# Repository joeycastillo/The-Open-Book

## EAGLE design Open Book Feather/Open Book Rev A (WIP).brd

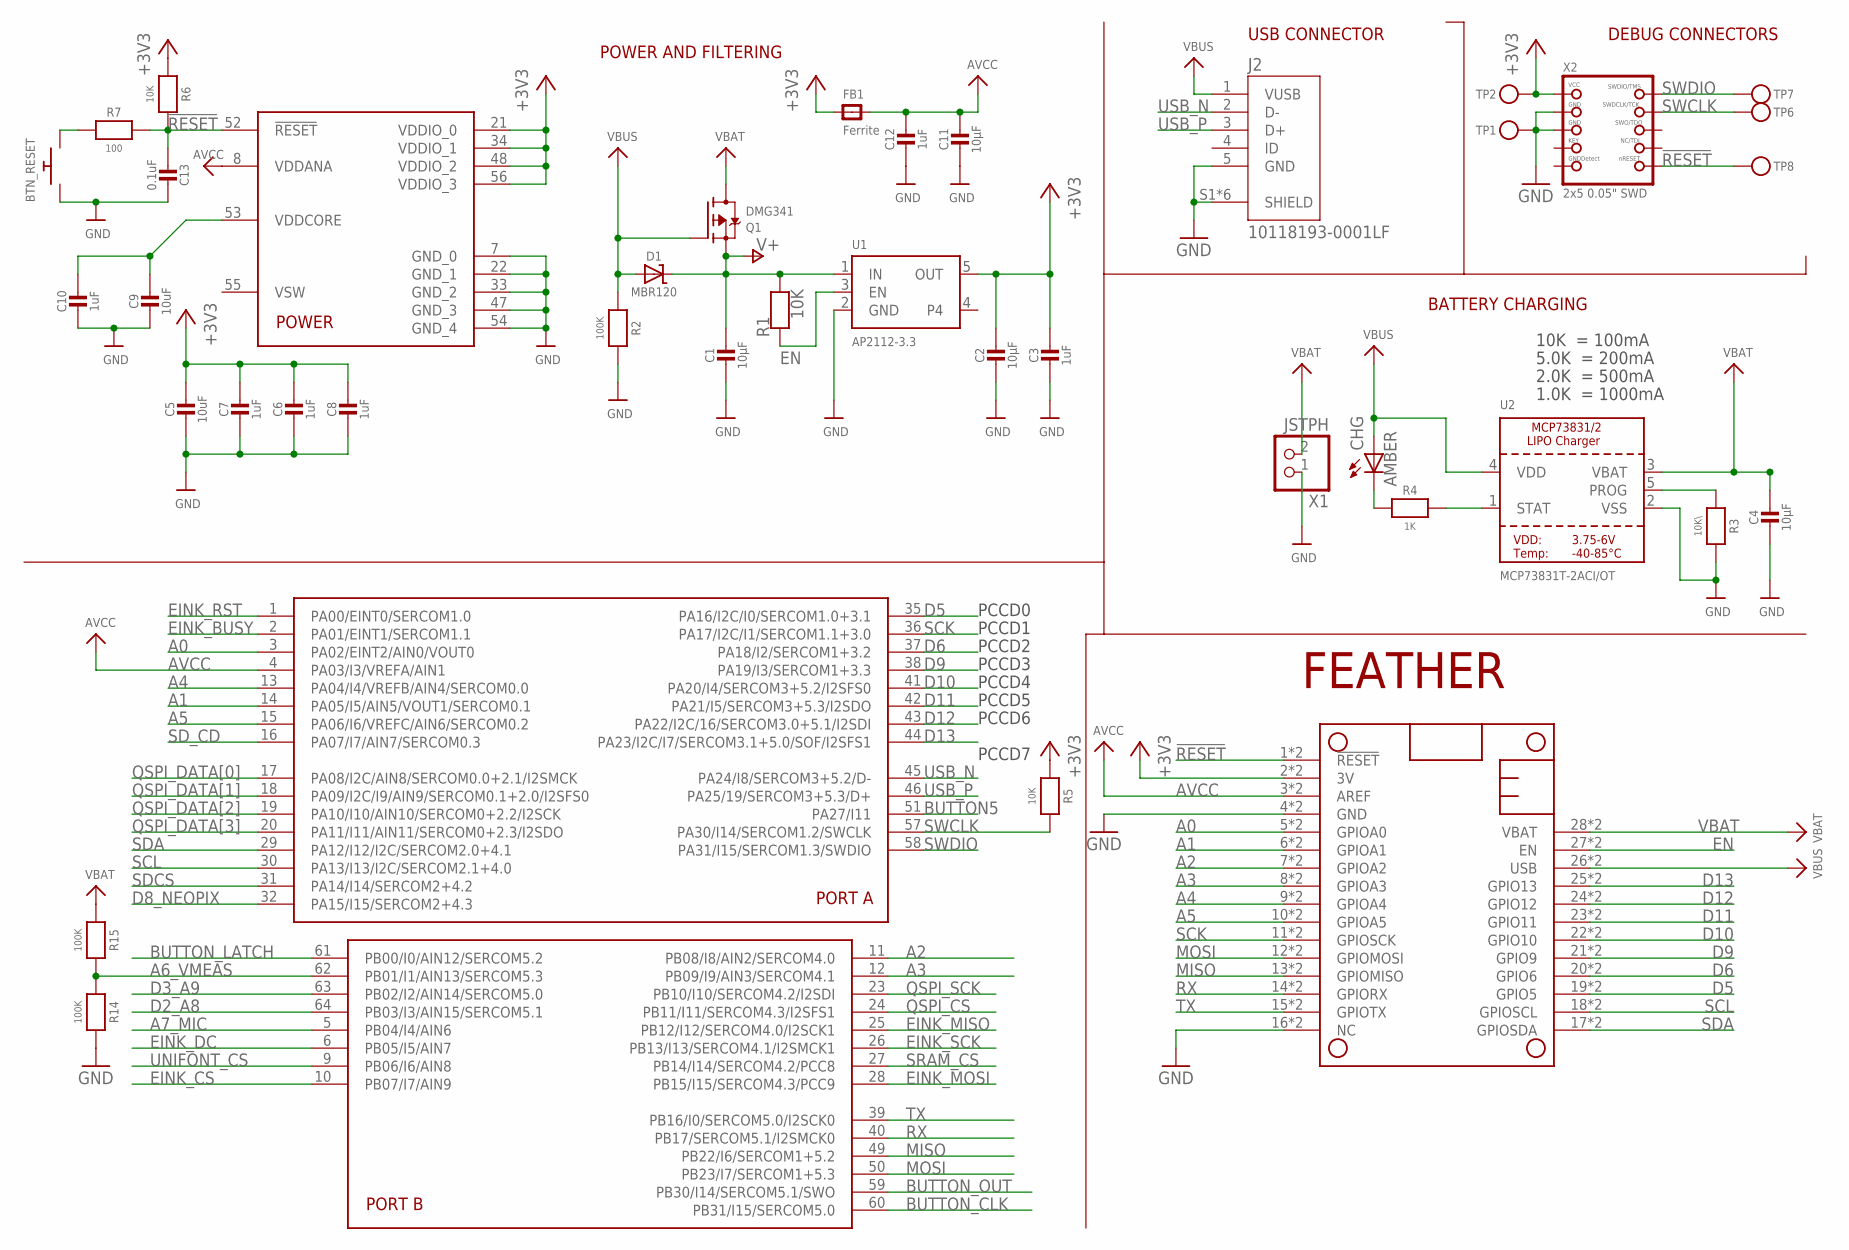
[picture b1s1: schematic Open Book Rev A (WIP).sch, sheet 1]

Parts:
BTN_RESET: SPST_TACTILE_SWITCHRA; TL3330AF130QG
C1, C2, C4, C11: 10µF; 0805-NO
C3, C7, C12: 1uF; 0805-NO
C5, C9: 10uF; 0805_10MGAP
C6, C8, C10: 1uF; 0805_10MGAP
C13: 0.1uF; 0805_10MGAP
CHG: AMBER; LED17X45_SIDEVIEW
D1: MBR120; SOD-123
FB1: Ferrite; 0805
J2: 10118193-0001LF; FCI_10118193-0001LF
MS1: FEATHERWING_SMTDUAL; FEATHERWING_SMT2
Q1: DMG341; SOT23-R
R1: 10K; 0805-NO
R2, R14, R15: 100K; 0805-NO
R3: 10K\; 0805-NO
R4: 1K; 0805-NO
R5, R6: 10K; 0805_10MGAP
R7: 100; 0805_10MGAP
TP1, TP2, TP6, TP7, TP8: TESTPOINTROUND2MMNO; TESTPOINT_ROUND_2MM_NO
U1: AP2112-3.3; SOT23-5
U2: MCP73831T-2ACI/OT; SOT23-5
U3: ATSAMD51J64-TQFP(10X10); TQFP64-10X10
X1: JSTPH; JSTPH2
X2: 2x5 0.05" SWD; 2X05_1.27MM_BOX_POSTS

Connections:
!RESET: C13.2, MS1.1 (!RESET), MS1.1' (!RESET), R6.2, R7.2, TP8.P$1, U3.52 (!RESET), X2.10 (NRESET)
+3V3: C2.1, C3.1, C5.1, C6.1, C7.1, C8.1, FB1.1, MS1.2 (3V), MS1.2' (3V), R5.1, R6.1, TP2.P$1, U1.5 (OUT), U3.21 (VDDIO_0), U3.34 (VDDIO_1), U3.48 (VDDIO_2), U3.56 (VDDIO_3), X2.1 (VCC); also elsewhere on the board
A0: MS1.5 (GPIOA0), MS1.5' (GPIOA0), U3.3 (PA02/EINT2/AIN0/VOUT0); also elsewhere on the board
A1: MS1.6 (GPIOA1), MS1.6' (GPIOA1), U3.14 (PA05/I5/AIN5/VOUT1/SERCOM0.1); also elsewhere on the board
A2: MS1.7 (GPIOA2), MS1.7' (GPIOA2), U3.11 (PB08/I8/AIN2/SERCOM4.0)
A3: MS1.8 (GPIOA3), MS1.8' (GPIOA3), U3.12 (PB09/I9/AIN3/SERCOM4.1)
A4: MS1.9 (GPIOA4), MS1.9' (GPIOA4), U3.13 (PA04/I4/VREFB/AIN4/SERCOM0.0)
A5: MS1.10 (GPIOA5), MS1.10' (GPIOA5), U3.15 (PA06/I6/VREFC/AIN6/SERCOM0.2)
A6_VMEAS: R14.1, R15.2, U3.62 (PB01/I1/AIN13/SERCOM5.3)
A7_MIC: U3.5 (PB04/I4/AIN6); also elsewhere on the board
AVCC: C11.1, C12.1, FB1.2, MS1.3 (AREF), MS1.3' (AREF), U3.4 (PA03/I3/VREFA/AIN1), U3.8 (VDDANA)
BUTTON5: U3.51 (PA27/I11); also elsewhere on the board
BUTTON_CLK: U3.60 (PB31/I15/SERCOM5.0); also elsewhere on the board
BUTTON_LATCH: U3.61 (PB00/I0/AIN12/SERCOM5.2); also elsewhere on the board
BUTTON_OUT: U3.59 (PB30/I14/SERCOM5.1/SWO); also elsewhere on the board
D2_A8: U3.64 (PB03/I3/AIN15/SERCOM5.1); also elsewhere on the board
D3_A9: U3.63 (PB02/I2/AIN14/SERCOM5.0); also elsewhere on the board
D5: MS1.19 (GPIO5), MS1.19' (GPIO5), U3.35 (PA16/I2C/I0/SERCOM1.0+3.1)
D6: MS1.20 (GPIO6), MS1.20' (GPIO6), U3.37 (PA18/I2/SERCOM1+3.2)
D8_NEOPIX: U3.32 (PA15/I15/SERCOM2+4.3); also elsewhere on the board
D9: MS1.21 (GPIO9), MS1.21' (GPIO9), U3.38 (PA19/I3/SERCOM1+3.3)
D10: MS1.22 (GPIO10), MS1.22' (GPIO10), U3.41 (PA20/I4/SERCOM3+5.2/I2SFS0)
D11: MS1.23 (GPIO11), MS1.23' (GPIO11), U3.42 (PA21/I5/SERCOM3+5.3/I2SDO)
D12: MS1.24 (GPIO12), MS1.24' (GPIO12), U3.43 (PA22/I2C/16/SERCOM3.0+5.1/I2SDI)
D13: MS1.25 (GPIO13), MS1.25' (GPIO13), U3.44 (PA23/I2C/I7/SERCOM3.1+5.0/SOF/I2SFS1); also elsewhere on the board
EINK_BUSY: U3.2 (PA01/EINT1/SERCOM1.1); also elsewhere on the board
EINK_CS: U3.10 (PB07/I7/AIN9); also elsewhere on the board
EINK_DC: U3.6 (PB05/I5/AIN7); also elsewhere on the board
EINK_MISO: U3.25 (PB12/I12/SERCOM4.0/I2SCK1); also elsewhere on the board
EINK_MOSI: U3.28 (PB15/I15/SERCOM4.3/PCC9); also elsewhere on the board
EINK_RST: U3.1 (PA00/EINT0/SERCOM1.0); also elsewhere on the board
EINK_SCK: U3.26 (PB13/I13/SERCOM4.1/I2SMCK1); also elsewhere on the board
EN: MS1.27 (EN), MS1.27' (EN), R1.1, U1.3 (EN); also elsewhere on the board
GND: BTN_RESET.P$1, C1.2, C2.2, C3.2, C4.2, C5.2, C6.2, C7.2, C8.2, C9.2, C10.2, C11.2, C12.2, C13.1, J2.5 (GND), J2.S1 (SHIELD), J2.S2 (SHIELD), J2.S3 (SHIELD), J2.S4 (SHIELD), J2.S5 (SHIELD), J2.S6 (SHIELD), MS1.4 (GND), MS1.4' (GND), MS1.16 (NC), MS1.16' (NC), R2.2, R3.2, R14.2, TP1.P$1, U1.2 (GND), U2.2 (VSS), U3.7 (GND_0), U3.22 (GND_1), U3.33 (GND_2), U3.47 (GND_3), U3.54 (GND_4), X1.1, X2.3 (GND), X2.5 (GND); also elsewhere on the board
MISO: MS1.13 (GPIOMISO), MS1.13' (GPIOMISO), U3.49 (PB22/I6/SERCOM1+5.2); also elsewhere on the board
MOSI: MS1.12 (GPIOMOSI), MS1.12' (GPIOMOSI), U3.50 (PB23/I7/SERCOM1+5.3); also elsewhere on the board
unnamed: BTN_RESET.P$2, R7.1
unnamed: CHG.K (C), R4.1
unnamed: R4.2, U2.1 (STAT)
PROG: R3.1, U2.5 (PROG)
QSPI_CS: U3.24 (PB11/I11/SERCOM4.3/I2SFS1); also elsewhere on the board
QSPI_DATA[0]: U3.17 (PA08/I2C/AIN8/SERCOM0.0+2.1/I2SMCK); also elsewhere on the board
QSPI_DATA[1]: U3.18 (PA09/I2C/I9/AIN9/SERCOM0.1+2.0/I2SFS0); also elsewhere on the board
QSPI_DATA[2]: U3.19 (PA10/I10/AIN10/SERCOM0+2.2/I2SCK); also elsewhere on the board
QSPI_DATA[3]: U3.20 (PA11/I11/AIN11/SERCOM0+2.3/I2SDO); also elsewhere on the board
QSPI_SCK: U3.23 (PB10/I10/SERCOM4.2/I2SDI); also elsewhere on the board
RX: MS1.14 (GPIORX), MS1.14' (GPIORX), U3.40 (PB17/SERCOM5.1/I2SMCK0); also elsewhere on the board
SCK: MS1.11 (GPIOSCK), MS1.11' (GPIOSCK), U3.36 (PA17/I2C/I1/SERCOM1.1+3.0); also elsewhere on the board
SCL: MS1.18 (GPIOSCL), MS1.18' (GPIOSCL), U3.30 (PA13/I13/I2C/SERCOM2.1+4.0); also elsewhere on the board
SDA: MS1.17 (GPIOSDA), MS1.17' (GPIOSDA), U3.29 (PA12/I12/I2C/SERCOM2.0+4.1); also elsewhere on the board
SDCS: U3.31 (PA14/I14/SERCOM2+4.2); also elsewhere on the board
SD_CD: U3.16 (PA07/I7/AIN7/SERCOM0.3); also elsewhere on the board
SRAM_CS: U3.27 (PB14/I14/SERCOM4.2/PCC8); also elsewhere on the board
SWCLK: R5.2, TP6.P$1, U3.57 (PA30/I14/SERCOM1.2/SWCLK), X2.4 (SWDCLK)
SWDIO: TP7.P$1, U3.58 (PA31/I15/SERCOM1.3/SWDIO), X2.2 (SWDIO)
TX: MS1.15 (GPIOTX), MS1.15' (GPIOTX), U3.39 (PB16/I0/SERCOM5.0/I2SCK0); also elsewhere on the board
UNIFONT_CS: U3.9 (PB06/I6/AIN8); also elsewhere on the board
USB_N: J2.2 (D-), U3.45 (PA24/I8/SERCOM3+5.2/D-)
USB_P: J2.3 (D+), U3.46 (PA25/19/SERCOM3+5.3/D+)
V+: C1.1, D1.C, Q1.2 (S), R1.2, U1.1 (IN); also elsewhere on the board
VBAT: C4.1, MS1.28 (VBAT), MS1.28' (VBAT), Q1.3 (D), R15.1, U2.3 (VBAT), X1.2
VBUS: CHG.A, D1.A, J2.1 (VUSB), MS1.26 (USB), MS1.26' (USB), Q1.1 (G), R2.1, U2.4 (VDD)
VDDCORE2: C9.1, C10.1, U3.53 (VDDCORE)

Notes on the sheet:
FEATHER
PCCD0
PCCD1
PCCD2
PCCD3
PCCD4
PCCD5
PCCD6
PCCD7
POWER AND FILTERING
10K = 100mA
5.0K = 200mA
2.0K = 500mA
1.0K = 1000mA
BATTERY CHARGING
DEBUG CONNECTORS
USB CONNECTOR

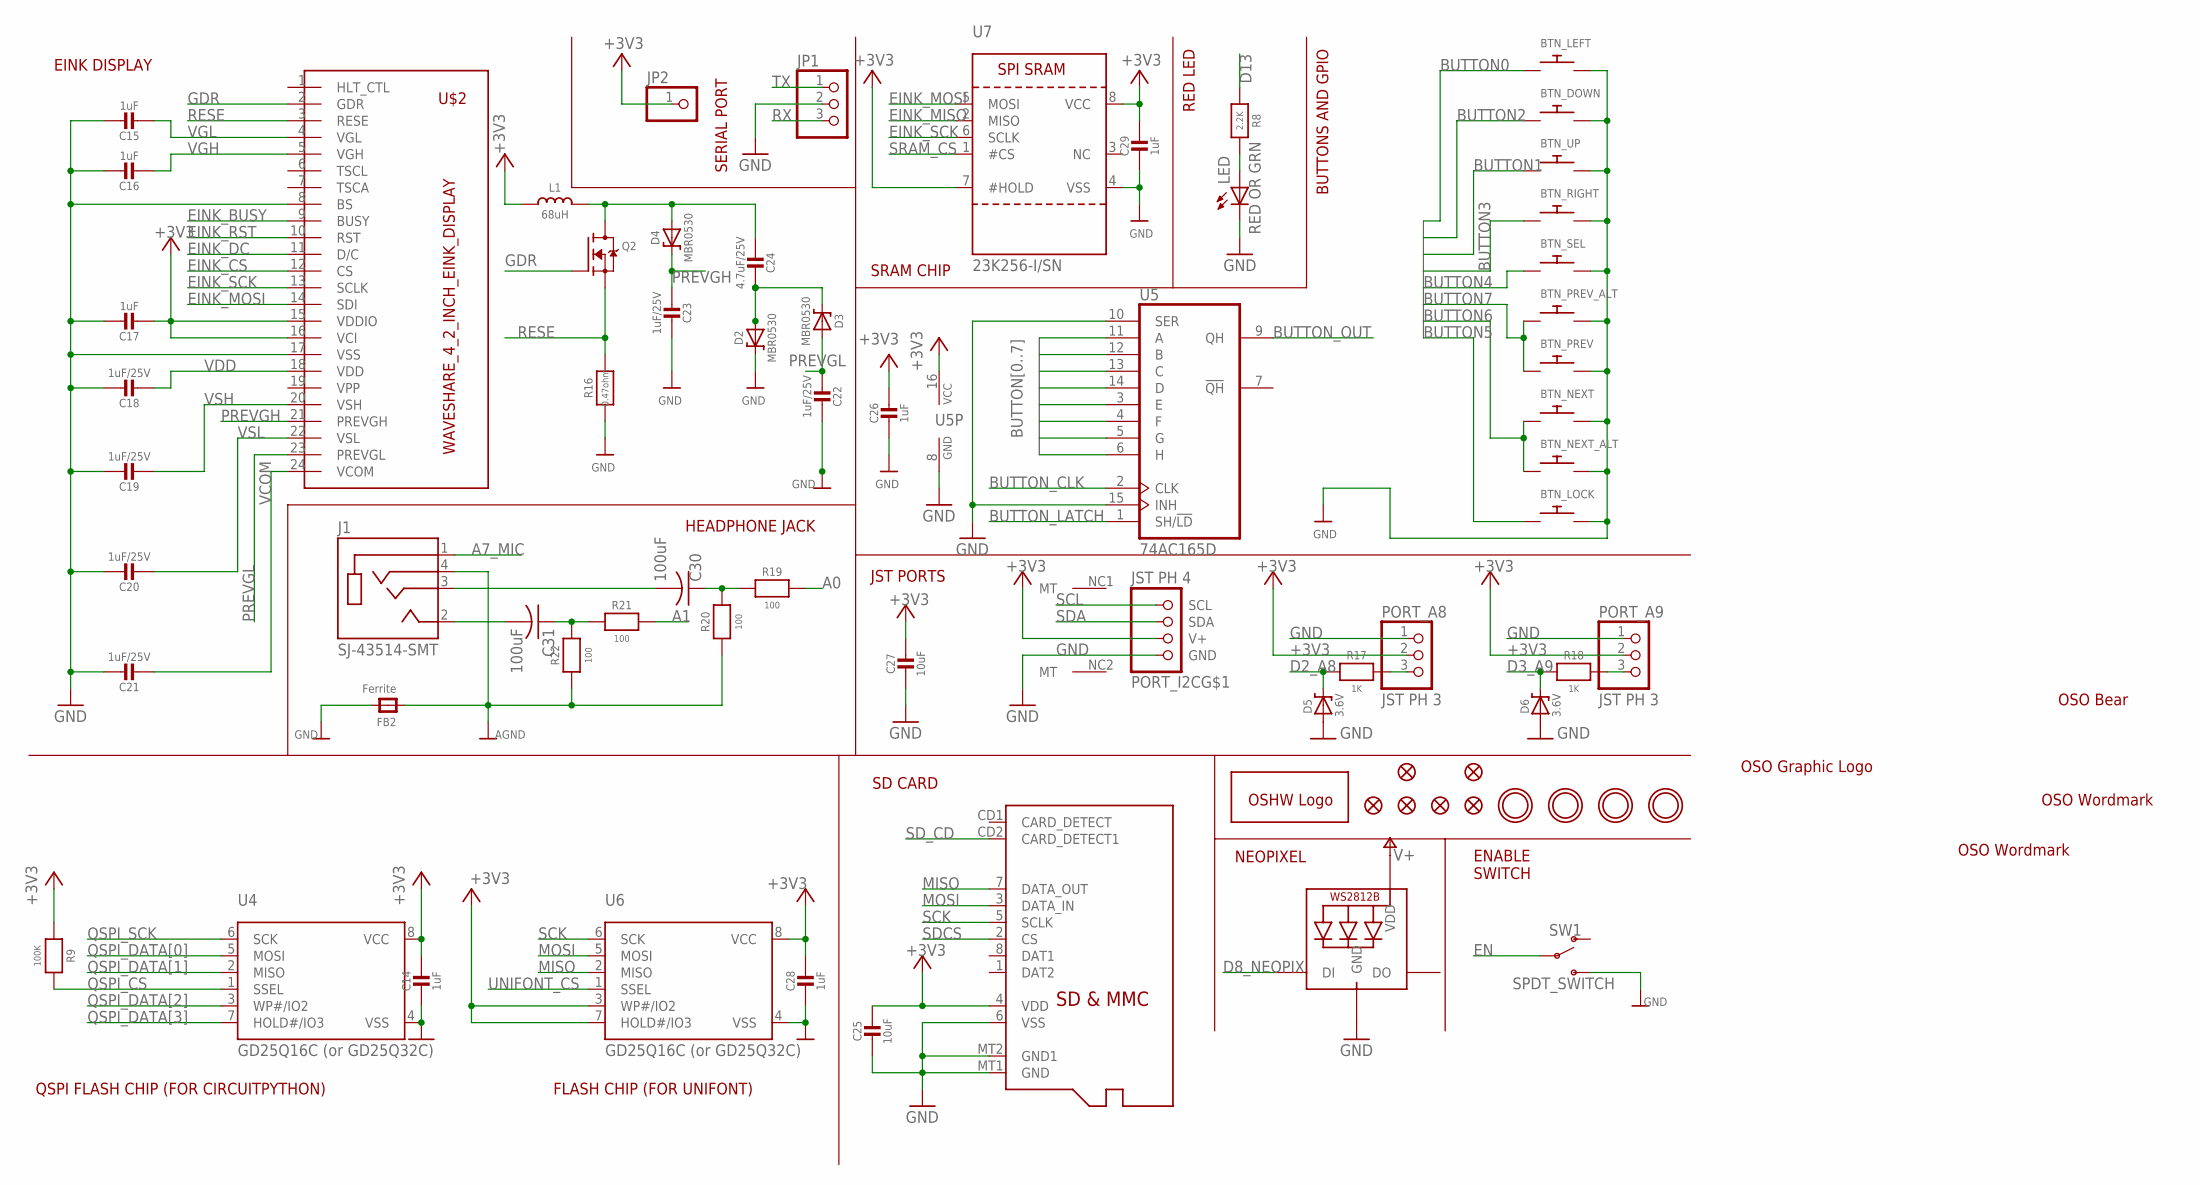
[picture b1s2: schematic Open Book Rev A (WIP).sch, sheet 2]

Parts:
BTN_DOWN: MJTP1250_SPST_SWITCH; MJTP1250
BTN_LEFT: MJTP1250_SPST_SWITCH; MJTP1250
BTN_LOCK: SPST_TACTILE_SWITCHRA; TL3330AF130QG
BTN_NEXT: MJTP1250_SPST_SWITCH; MJTP1250
BTN_NEXT_ALT: SPST_TACTILE_SWITCHRA; TL3330AF130QG
BTN_PREV: MJTP1250_SPST_SWITCH; MJTP1250
BTN_PREV_ALT: SPST_TACTILE_SWITCHRA; TL3330AF130QG
BTN_RIGHT: MJTP1250_SPST_SWITCH; MJTP1250
BTN_SEL: MJTP1250_SPST_SWITCH; MJTP1250
BTN_UP: MJTP1250_SPST_SWITCH; MJTP1250
C14, C15, C16, C17: 1uF; 0805-NO
C18, C19, C20, C21, C22, C23: 1uF/25V; 0805-NO
C24: 4.7uF/25V; 0805-NO
C25: 10uF; 0805_10MGAP
C26, C28, C29: 1uF; 0805_10MGAP
C27: 10uF; 0805-NO
C30, C31: 100uF; C1210
D2, D3, D4: MBR0530; SOD-123
D5, D6: 3.6V; SOD-123
FB2: Ferrite; 0805
FID1, FID2, FID3, FID4, FID5, FID6: FIDUCIAL_1MM
GOLD_ORB_SM1: OSHWLOGOLOGO5MM; OSHW_5MM
J1: SJ-43514-SMT; CUI_SJ-43514-SMT
JP1: PINHD-1X3; 1X03
JP2: PINHD-1X1; 1X01
L1: 68uH; INDUCTOR_4X4MM_NR401
LED: RED OR GRN; LED17X45_SIDEVIEW
MICROSD: MICROSD
PORT_A8, PORT_A9: JST PH 3; JSTPH3
PORT_I2C: JST PH 4; JSTPH4
Q2: IRLML0100; SOT23-3
R8: 2.2K; 0805-NO
R9: 100K; 0805-NO
R16: 0.47ohm; 0805_10MGAP
R17, R18: 1K; _0805MP
R19, R20, R21, R22: 100; 0805-NO
STATUS: WS2812B; LED5MMRGB
SW1: SPDT_SWITCH; A10767
U4: GD25Q16C (or GD25Q32C); SOIC8_150MIL
U5: 74AC165D; SO16
U6: GD25Q16C (or GD25Q32C); MICROBUILDER_SOIC8_150MIL
U7: 23K256-I/SN; SOIC8_150MIL
U$1, U$4, U$5, U$7: MOUNTINGHOLE2.5; MOUNTINGHOLE_2.5_PLATED
U$2: WAVESHARE_4_2_INCH_EINK_DISPLAY; EINK_DISPLAY_4_2IN
U$44: OSO_GRAPHIC
U$45: OSO_BEAR; OSO_BEAR_750MIL
U$47: OSO_TEXT; OSO_TEXT_435MIL
U$48: OSO_TEXTOSO_TEXT_ONELINE_125MIL; OSO_ONELINE_125MIL

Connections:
+3V3: C14.1, C17.2, C25.1, C26.1, C27.1, C28.1, C29.1, JP2.1, L1.P$2 (2), MICROSD.4 (VDD), PORT_A8.2, PORT_A9.2, PORT_I2C.2 (V+), R9.1, U4.8 (VCC), U5.16 (VCC), U6.3 (WP#/IO2), U6.7 (HOLD#/IO3), U6.8 (VCC), U7.7 (#HOLD), U7.8 (VCC), U$2.15 (VDDIO), U$2.16 (VCI); also elsewhere on the board
A0: R19.2; also elsewhere on the board
A1: R21.2; also elsewhere on the board
A7_MIC: J1.1 (SLEEVE); also elsewhere on the board
A8_: PORT_A8.3, R17.1
A9_: PORT_A9.3, R18.1
AGND: FB2.1, J1.4 (RING2), R20.1, R22.1
AUDIO_LEFT: C31.2, J1.2 (TIP)
AUDIO_RIGHT: C30.2, J1.3 (RING1)
BUTTON0: BTN_LEFT.P$1, U5.11 (A)
BUTTON1: BTN_UP.P$1, U5.12 (B)
BUTTON2: BTN_DOWN.P$1, U5.13 (C)
BUTTON3: BTN_RIGHT.P$1, U5.14 (D)
BUTTON4: BTN_SEL.P$1, U5.3 (E)
BUTTON5: BTN_LOCK.P$1, U5.4 (F); also elsewhere on the board
BUTTON6: BTN_NEXT.P$1, BTN_NEXT_ALT.P$1, U5.5 (G)
BUTTON7: BTN_PREV.P$1, BTN_PREV_ALT.P$1, U5.6 (H)
BUTTON_CLK: U5.2 (CLK); also elsewhere on the board
BUTTON_LATCH: U5.1 (SH/!LD); also elsewhere on the board
BUTTON_OUT: U5.9 (QH); also elsewhere on the board
D2_A8: D5.C, R17.2; also elsewhere on the board
D3_A9: D6.C, R18.2; also elsewhere on the board
D8_NEOPIX: STATUS.4 (DI); also elsewhere on the board
D13: R8.1; also elsewhere on the board
EINK_BUSY: U$2.9 (BUSY); also elsewhere on the board
EINK_CS: U$2.12 (CS); also elsewhere on the board
EINK_DC: U$2.11 (D/C); also elsewhere on the board
EINK_MISO: U7.2 (MISO); also elsewhere on the board
EINK_MOSI: U7.5 (MOSI), U$2.14 (SDI); also elsewhere on the board
EINK_RST: U$2.10 (RST); also elsewhere on the board
EINK_SCK: U7.6 (SCLK), U$2.13 (SCLK); also elsewhere on the board
EN: SW1.P$2; also elsewhere on the board
GDR: Q2.1 (G), U$2.2 (GDR)
GND: BTN_DOWN.P$2, BTN_LEFT.P$2, BTN_LOCK.P$2, BTN_NEXT.P$2, BTN_NEXT_ALT.P$2, BTN_PREV.P$2, BTN_PREV_ALT.P$2, BTN_RIGHT.P$2, BTN_SEL.P$2, BTN_UP.P$2, C14.2, C15.1, C16.1, C17.1, C18.1, C19.1, C20.1, C21.1, C22.2, C23.2, C25.2, C26.2, C27.2, C28.2, C29.2, D2.C, D5.A, D6.A, FB2.2, JP1.2, LED.K (C), MICROSD.6 (VSS), MICROSD.MT1 (GND), MICROSD.MT2 (GND1), PORT_A8.1, PORT_A9.1, PORT_I2C.1 (GND), R16.2, STATUS.2 (GND), SW1.P$3 (S), U4.4 (VSS), U5.8 (GND), U5.10 (SER), U5.15 (INH), U6.4 (VSS), U7.4 (VSS), U$2.8 (BS), U$2.17 (VSS); also elsewhere on the board
MISO: MICROSD.7 (DATA_OUT), U6.2 (MISO); also elsewhere on the board
MOSI: MICROSD.3 (DATA_IN), U6.5 (MOSI); also elsewhere on the board
unnamed: C24.2, D2.A, D3.C
unnamed: C24.1, D4.A, L1.P$1 (1), Q2.3 (D)
unnamed: LED.A, R8.2
unnamed: C31.1, R21.1, R22.2
unnamed: C30.1, R19.1, R20.2
PREVGH: C23.1, D4.C, U$2.21 (PREVGH)
PREVGL: C22.1, D3.A, U$2.23 (PREVGL)
QSPI_CS: R9.2, U4.1 (SSEL); also elsewhere on the board
QSPI_DATA[0]: U4.5 (MOSI); also elsewhere on the board
QSPI_DATA[1]: U4.2 (MISO); also elsewhere on the board
QSPI_DATA[2]: U4.3 (WP#/IO2); also elsewhere on the board
QSPI_DATA[3]: U4.7 (HOLD#/IO3); also elsewhere on the board
QSPI_SCK: U4.6 (SCK); also elsewhere on the board
RESE: Q2.2 (S), R16.1, U$2.3 (RESE)
RX: JP1.3; also elsewhere on the board
SCK: MICROSD.5 (SCLK), U6.6 (SCK); also elsewhere on the board
SCL: PORT_I2C.4 (SCL); also elsewhere on the board
SDA: PORT_I2C.3 (SDA); also elsewhere on the board
SDCS: MICROSD.2 (CS); also elsewhere on the board
SD_CD: MICROSD.CD2 (CARD_DETECT1); also elsewhere on the board
SRAM_CS: U7.1 (#CS); also elsewhere on the board
TX: JP1.1; also elsewhere on the board
UNIFONT_CS: U6.1 (SSEL); also elsewhere on the board
V+: STATUS.3 (VDD); also elsewhere on the board
VCOM: C21.2, U$2.24 (VCOM)
VDD: C18.2, U$2.18 (VDD)
VGH: C16.2, U$2.5 (VGH)
VGL: C15.2, U$2.4 (VGL)
VSH: C19.2, U$2.20 (VSH)
VSL: C20.2, U$2.22 (VSL)

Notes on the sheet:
SD CARD
EINK DISPLAY
HEADPHONE JACK
ENABLE SWITCH
BUTTONS AND GPIO
JST PORTS
QSPI FLASH CHIP (FOR CIRCUITPYTHON)
SERIAL PORT
RED LED
FLASH CHIP (FOR UNIFONT)
NEOPIXEL
SRAM CHIP

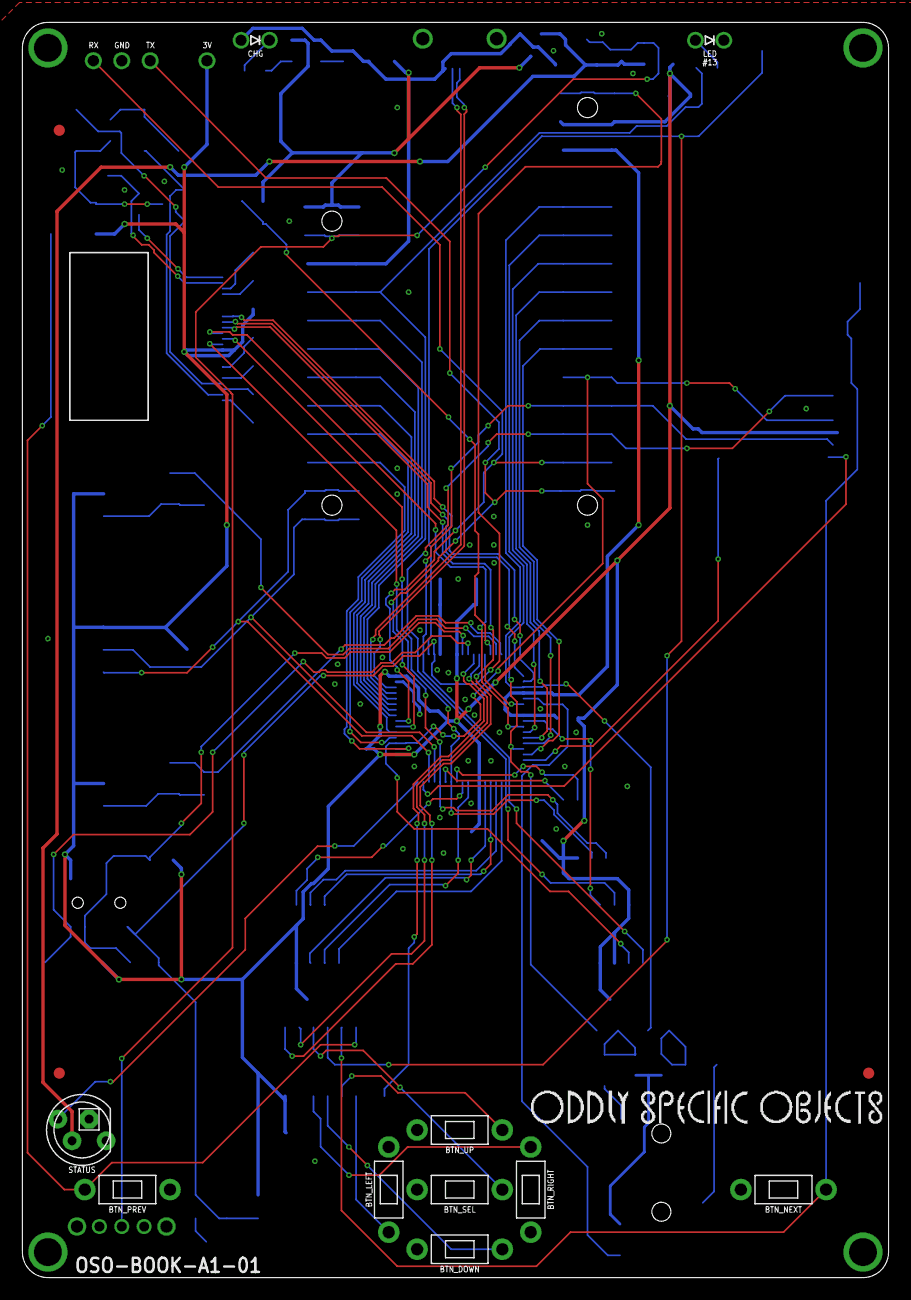
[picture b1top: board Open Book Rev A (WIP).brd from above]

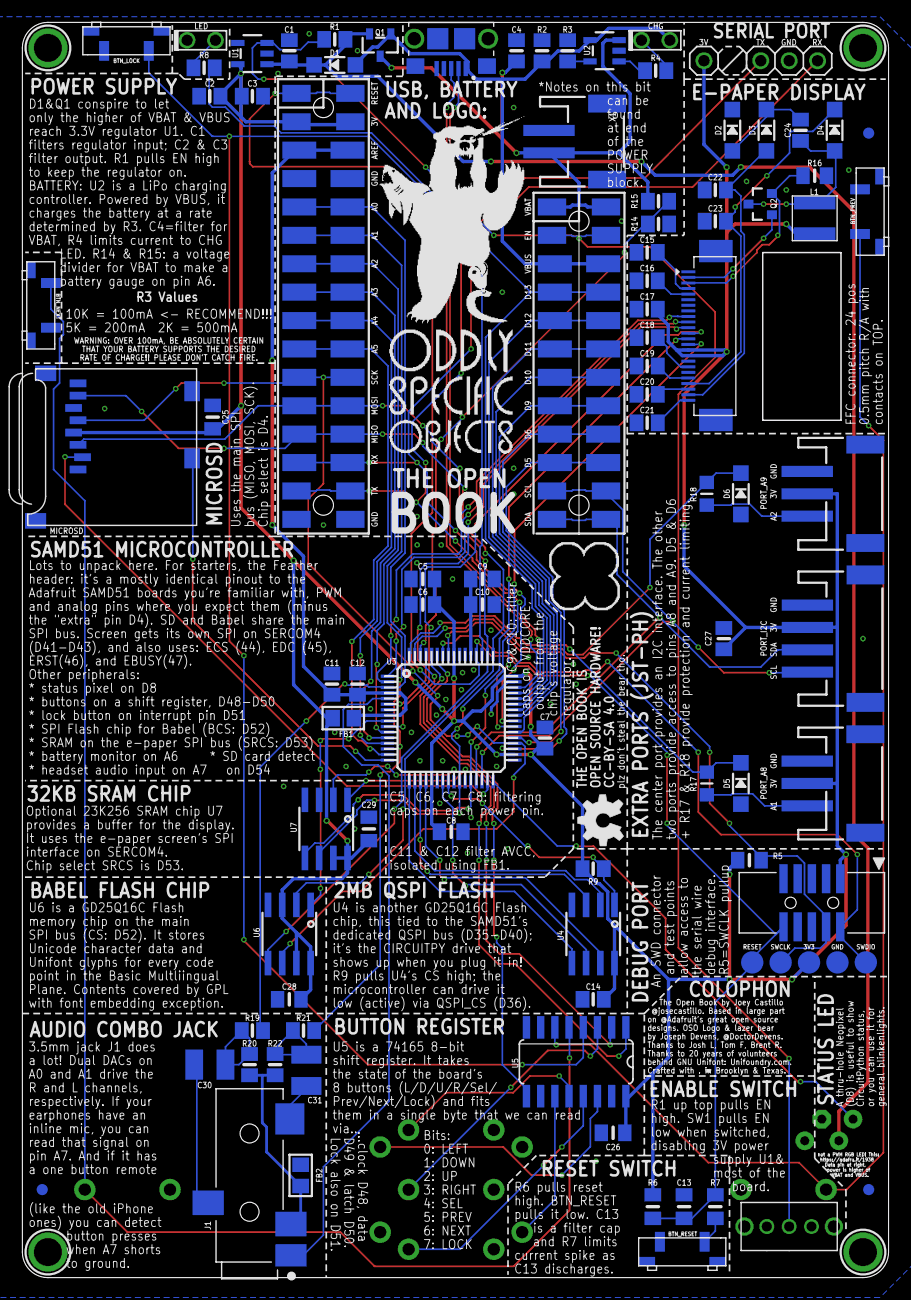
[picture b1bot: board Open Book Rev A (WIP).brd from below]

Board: 2 copper layers, 77.5 x 112.3 mm, 114 parts (101 on the bottom side), 90 nets.

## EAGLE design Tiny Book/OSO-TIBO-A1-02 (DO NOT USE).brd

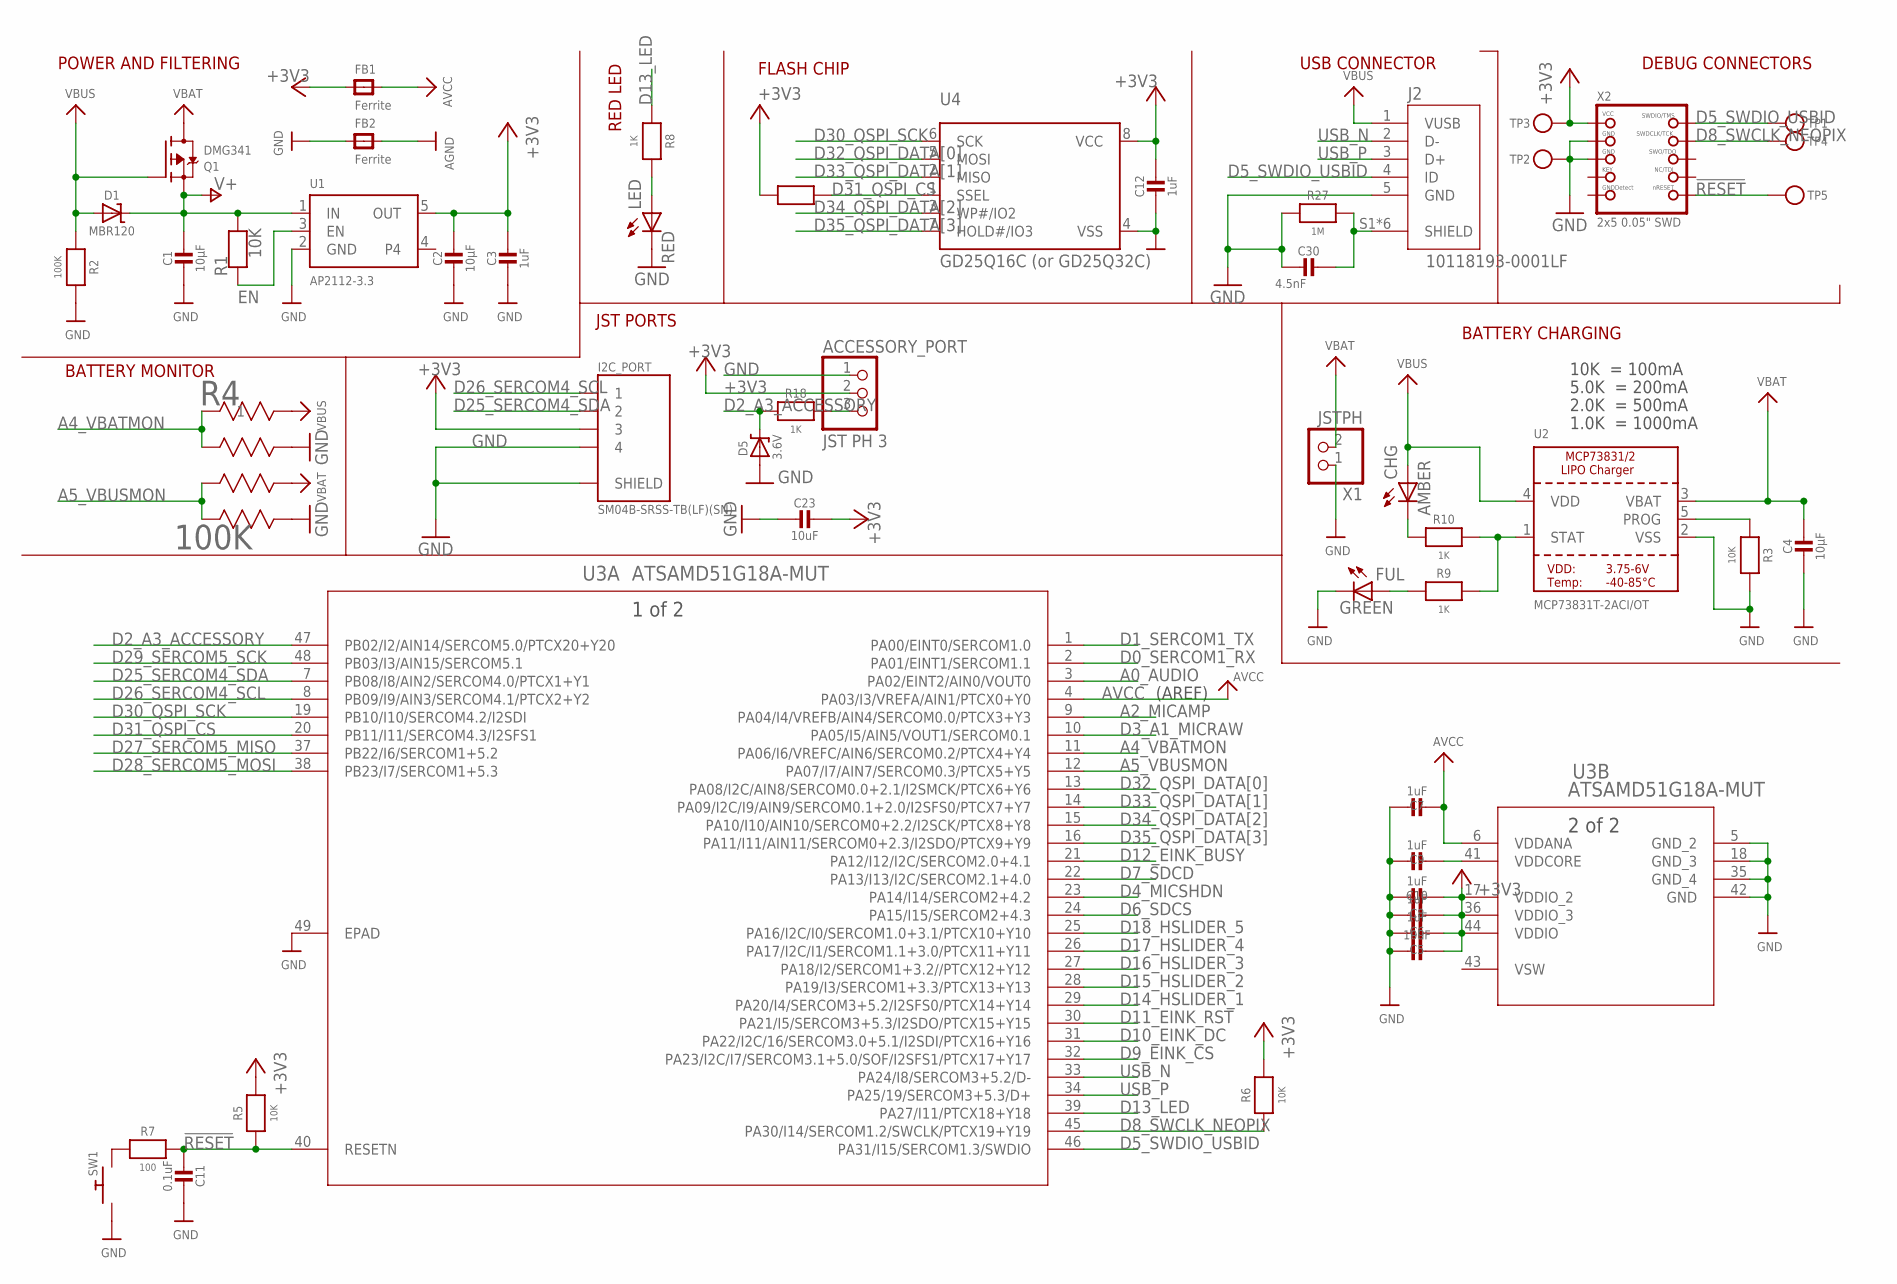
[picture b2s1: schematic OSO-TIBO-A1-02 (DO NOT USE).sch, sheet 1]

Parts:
ACCESSORY_PORT: JST PH 3; JSTPH3
C1, C2, C4: 10µF; 0805-NO
C3, C6, C7: 1uF; 0805-NO
C5, C23: 10uF; 0805-NO
C8, C9, C10, C12: 1uF; 0805_10MGAP
C11: 0.1uF; 0805_10MGAP
C30: 4.5nF; 0805-NO
CHG: AMBER; CHIP-LED0805_REVERSEMOUNT
D1: MBR120; SOD-123
D5: 3.6V; SOD-123
FB1, FB2: Ferrite; 0805
FUL: GREEN; CHIP-LED0805_REVERSEMOUNT
I2C_PORT: SM04B-SRSS-TB(LF)(SN); JST_SM04B-SRSS-TB(LF)(SN)
J2: 10118193-0001LF; FCI_10118193-0001LF
LED: RED; CHIP-LED0805_REVERSEMOUNT
Q1: DMG341; SOT23-R
R1, R3, R5, R6, R11: 10K; 0805-NO
R2: 100K; 0805-NO
R4: 100K; EXBV8V
R7: 100; 0805_10MGAP
R8, R9, R10: 1K; 0805-NO
R18: 1K; _0805MP
R27: 1M; 0805-NO
SW1: SPST_TACTILE_SWITCHRA-THRU; MJTP1117
TP1, TP2, TP3, TP4, TP5: TESTPOINTROUND2MMNO; TESTPOINT_ROUND_2MM_NO
U1: AP2112-3.3; SOT23-5
U2: MCP73831T-2ACI/OT; SOT23-5
U3: ATSAMD51G18A-MUT; QFN48_7X7MC
U4: GD25Q16C (or GD25Q32C); MICROBUILDER_SOIC8_150MIL
X1: JSTPH; JSTPH2
X2: 2x5 0.05" SWD; 2X05_1.27MM_BOX_POSTS

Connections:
!RESET: C11.2, R5.1, R7.2, TP5.P$1, U3.40 (RESETN), X2.10 (NRESET)
+3V3: ACCESSORY_PORT.2, C2.1, C3.1, C5.2, C6.2, C8.2, C10.2, C12.1, C23.1, FB1.1, I2C_PORT.3, R5.2, R6.2, R11.2, TP3.P$1, U1.5 (OUT), U3.17 (VDDIO_2), U3.36 (VDDIO_3), U3.44 (VDDIO), U4.8 (VCC), X2.1 (VCC); also elsewhere on the board
A0_AUDIO: U3.3 (PA02/EINT2/AIN0/VOUT0); also elsewhere on the board
A2_MICAMP: U3.9 (PA04/I4/VREFB/AIN4/SERCOM0.0/PTCX3+Y3); also elsewhere on the board
A4_VBATMON: R4.1, R4.2, U3.11 (PA06/I6/VREFC/AIN6/SERCOM0.2/PTCX4+Y4)
A5_VBUSMON: R4.3, R4.4, U3.12 (PA07/I7/AIN7/SERCOM0.3/PTCX5+Y5)
AGND: FB2.2; also elsewhere on the board
AVCC: C7.2, FB1.2, U3.4 (PA03/I3/VREFA/AIN1/PTCX0+Y0), U3.6 (VDDANA); also elsewhere on the board
D0_SERCOM1_RX: U3.2 (PA01/EINT1/SERCOM1.1); also elsewhere on the board
D1_SERCOM1_TX: U3.1 (PA00/EINT0/SERCOM1.0); also elsewhere on the board
D2_A3_ACCESSORY: D5.C, R18.2, U3.47 (PB02/I2/AIN14/SERCOM5.0/PTCX20+Y20)
D3_A1_MICRAW: U3.10 (PA05/I5/AIN5/VOUT1/SERCOM0.1); also elsewhere on the board
D4_MICSHDN: U3.23 (PA14/I14/SERCOM2+4.2); also elsewhere on the board
D5_SWDIO_USBID: J2.4 (ID), TP1.P$1, U3.46 (PA31/I15/SERCOM1.3/SWDIO), X2.2 (SWDIO)
D6_SDCS: U3.24 (PA15/I15/SERCOM2+4.3); also elsewhere on the board
D7_SDCD: U3.22 (PA13/I13/I2C/SERCOM2.1+4.0); also elsewhere on the board
D8_SWCLK_NEOPIX: R6.1, TP4.P$1, U3.45 (PA30/I14/SERCOM1.2/SWCLK/PTCX19+Y19), X2.4 (SWDCLK); also elsewhere on the board
D9_EINK_CS: U3.32 (PA23/I2C/I7/SERCOM3.1+5.0/SOF/I2SFS1/PT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); also elsewhere on the board
D10_EINK_DC: U3.31 (PA22/I2C/16/SERCOM3.0+5.1/I2SDI/PTCX16+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); also elsewhere on the board
D11_EINK_RST: U3.30 (PA21/I5/SERCOM3+5.3/I2SDO/PTCX15+Y15); also elsewhere on the board
D12_EINK_BUSY: U3.21 (PA12/I12/I2C/SERCOM2.0+4.1); also elsewhere on the board
D13_LED: R8.1, U3.39 (PA27/I11/PTCX18+Y18)
D14_HSLIDER_1: U3.29 (PA20/I4/SERCOM3+5.2/I2SFS0/PTCX14+Y14); also elsewhere on the board
D15_HSLIDER_2: U3.28 (PA19/I3/SERCOM1+3.3/PTCX13+Y13); also elsewhere on the board
D16_HSLIDER_3: U3.27 (PA18/I2/SERCOM1+3.2//PTCX12+Y12); also elsewhere on the board
D17_HSLIDER_4: U3.26 (PA17/I2C/I1/SERCOM1.1+3.0/PTCX11+Y11); also elsewhere on the board
D18_HSLIDER_5: U3.25 (PA16/I2C/I0/SERCOM1.0+3.1/PTCX10+Y10); also elsewhere on the board
D25_SERCOM4_SDA: I2C_PORT.2, U3.7 (PB08/I8/AIN2/SERCOM4.0/PTCX1+Y1)
D26_SERCOM4_SCL: I2C_PORT.1, U3.8 (PB09/I9/AIN3/SERCOM4.1/PTCX2+Y2)
D27_SERCOM5_MISO: U3.37 (PB22/I6/SERCOM1+5.2); also elsewhere on the board
D28_SERCOM5_MOSI: U3.38 (PB23/I7/SERCOM1+5.3); also elsewhere on the board
D29_SERCOM5_SCK: U3.48 (PB03/I3/AIN15/SERCOM5.1); also elsewhere on the board
D30_QSPI_SCK: U3.19 (PB10/I10/SERCOM4.2/I2SDI), U4.6 (SCK)
D31_QSPI_CS: R11.1, U3.20 (PB11/I11/SERCOM4.3/I2SFS1), U4.1 (SSEL)
D32_QSPI_DATA[0]: U3.13 (PA08/I2C/AIN8/SERCOM0.0+2.1/I2SMCK/PTCX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), U4.5 (MOSI)
D33_QSPI_DATA[1]: U3.14 (PA09/I2C/I9/AIN9/SERCOM0.1+2.0/I2SFS0/P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), U4.2 (MISO)
D34_QSPI_DATA[2]: U3.15 (PA10/I10/AIN10/SERCOM0+2.2/I2SCK/PTCX8+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), U4.3 (WP#/IO2)
D35_QSPI_DATA[3]: U3.16 (PA11/I11/AIN11/SERCOM0+2.3/I2SDO/PTCX9+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), U4.7 (HOLD#/IO3)
EN: R1.1, U1.3 (EN); also elsewhere on the board
GND: ACCESSORY_PORT.1, C1.2, C2.2, C3.2, C4.2, C5.1, C6.1, C7.1, C8.1, C9.1, C10.1, C11.1, C12.2, C23.2, C30.2, D5.A, FB2.1, FUL.C, I2C_PORT.4, I2C_PORT.S1 (SHIELD), I2C_PORT.S2 (SHIELD), J2.5 (GND), LED.C, R2.2, R3.2, R4.5, R4.7, R27.2, SW1.P$1, TP2.P$1, U1.2 (GND), U2.2 (VSS), U3.5 (GND_2), U3.18 (GND_3), U3.35 (GND_4), U3.42 (GND), U3.49 (EPAD), U4.4 (VSS), X1.1, X2.3 (GND), X2.5 (GND); also elsewhere on the board
unnamed: R7.1, SW1.P$2
unnamed: CHG.C, R10.1
unnamed: LED.A, R8.2
unnamed: FUL.A, R9.1
PROG: R3.1, U2.5 (PROG)
SHIELD: C30.1, J2.S1 (SHIELD), J2.S2 (SHIELD), J2.S3 (SHIELD), J2.S4 (SHIELD), J2.S5 (SHIELD), J2.S6 (SHIELD), R27.1
STAT: R9.2, R10.2, U2.1 (STAT)
USB_N: J2.2 (D-), U3.33 (PA24/I8/SERCOM3+5.2/D-)
USB_P: J2.3 (D+), U3.34 (PA25/19/SERCOM3+5.3/D+)
V+: C1.1, D1.C, Q1.2 (S), R1.2, U1.1 (IN)
VBAT: C4.1, Q1.3 (D), R4.6, U2.3 (VBAT), X1.2
VBUS: CHG.A, D1.A, J2.1 (VUSB), Q1.1 (G), R2.1, R4.8, U2.4 (VDD)
VDDCORE: C9.2, U3.41 (VDDCORE)
VSW: U3.43 (VSW)
_ACCESSORY: ACCESSORY_PORT.3, R18.1

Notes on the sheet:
POWER AND FILTERING
10K = 100mA
5.0K = 200mA
2.0K = 500mA
1.0K = 1000mA
BATTERY CHARGING
DEBUG CONNECTORS
USB CONNECTOR
BATTERY MONITOR
FLASH CHIP
RED LED
JST PORTS
(AREF)

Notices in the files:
Open Book Feather/Open Book Rev A (WIP).brd:
CC-BY-SA 4.0
Plane. Contents covered by GPL
Tiny Book/OSO-TIBO-A1-02 (DO NOT USE).brd:
CC-BY-SA 4.0 (except the bear!)
parts and their libraries:
PatternAgents-TouchWidgets: License : http://creativecommons.org/licenses/by-sa/4.0/ (Creative Commons 4.0)
PatternAgents-TouchWidgets: License : http://creativecommons.org/licenses/by-sa/3.1/ (Creative Commons 3.1)
COPYRIGHT: Copyright (C) 2018 Accelerated Designs. All rights reserved
